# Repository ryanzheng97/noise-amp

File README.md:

# noise-amp

A very high gain (80db or x10000) differential AC signal amplifier (LNA, pre-amplifier, noise amplifier, etc.) board based on EEVBlog community design.

[Original post](https://www.eevblog.com/forum/beginners/question-about-preamp-for-measuring-noise/msg98285/#msg98285)

Board is a 100x100mm 4-layer PCB which falls into the cheap sample tier at JLCPCB or PCBWay.

# Specs
- Gain: 80db nominal
- Bandwidth: <= 1MHz
- Power: +-18 to 35VDC, unregulated
- Connector: SMA for signal input and output, 2.54mm THT pads for power input.

Test was done with a 1M to 100R resistor divider in front of the input. Signal was a sigle-ended sine wave, so one of the input is shorted to ground. Channel 3 shows original signal before resistor divider. Channel 1 shows amplified output.

# Notes
- Use high quality electrolytic capacitors
- Keep away from transformers
- You can replace op-amps with other models that you have or like
- Avoid ground loop when using
- Ground one input if using sigle-ended

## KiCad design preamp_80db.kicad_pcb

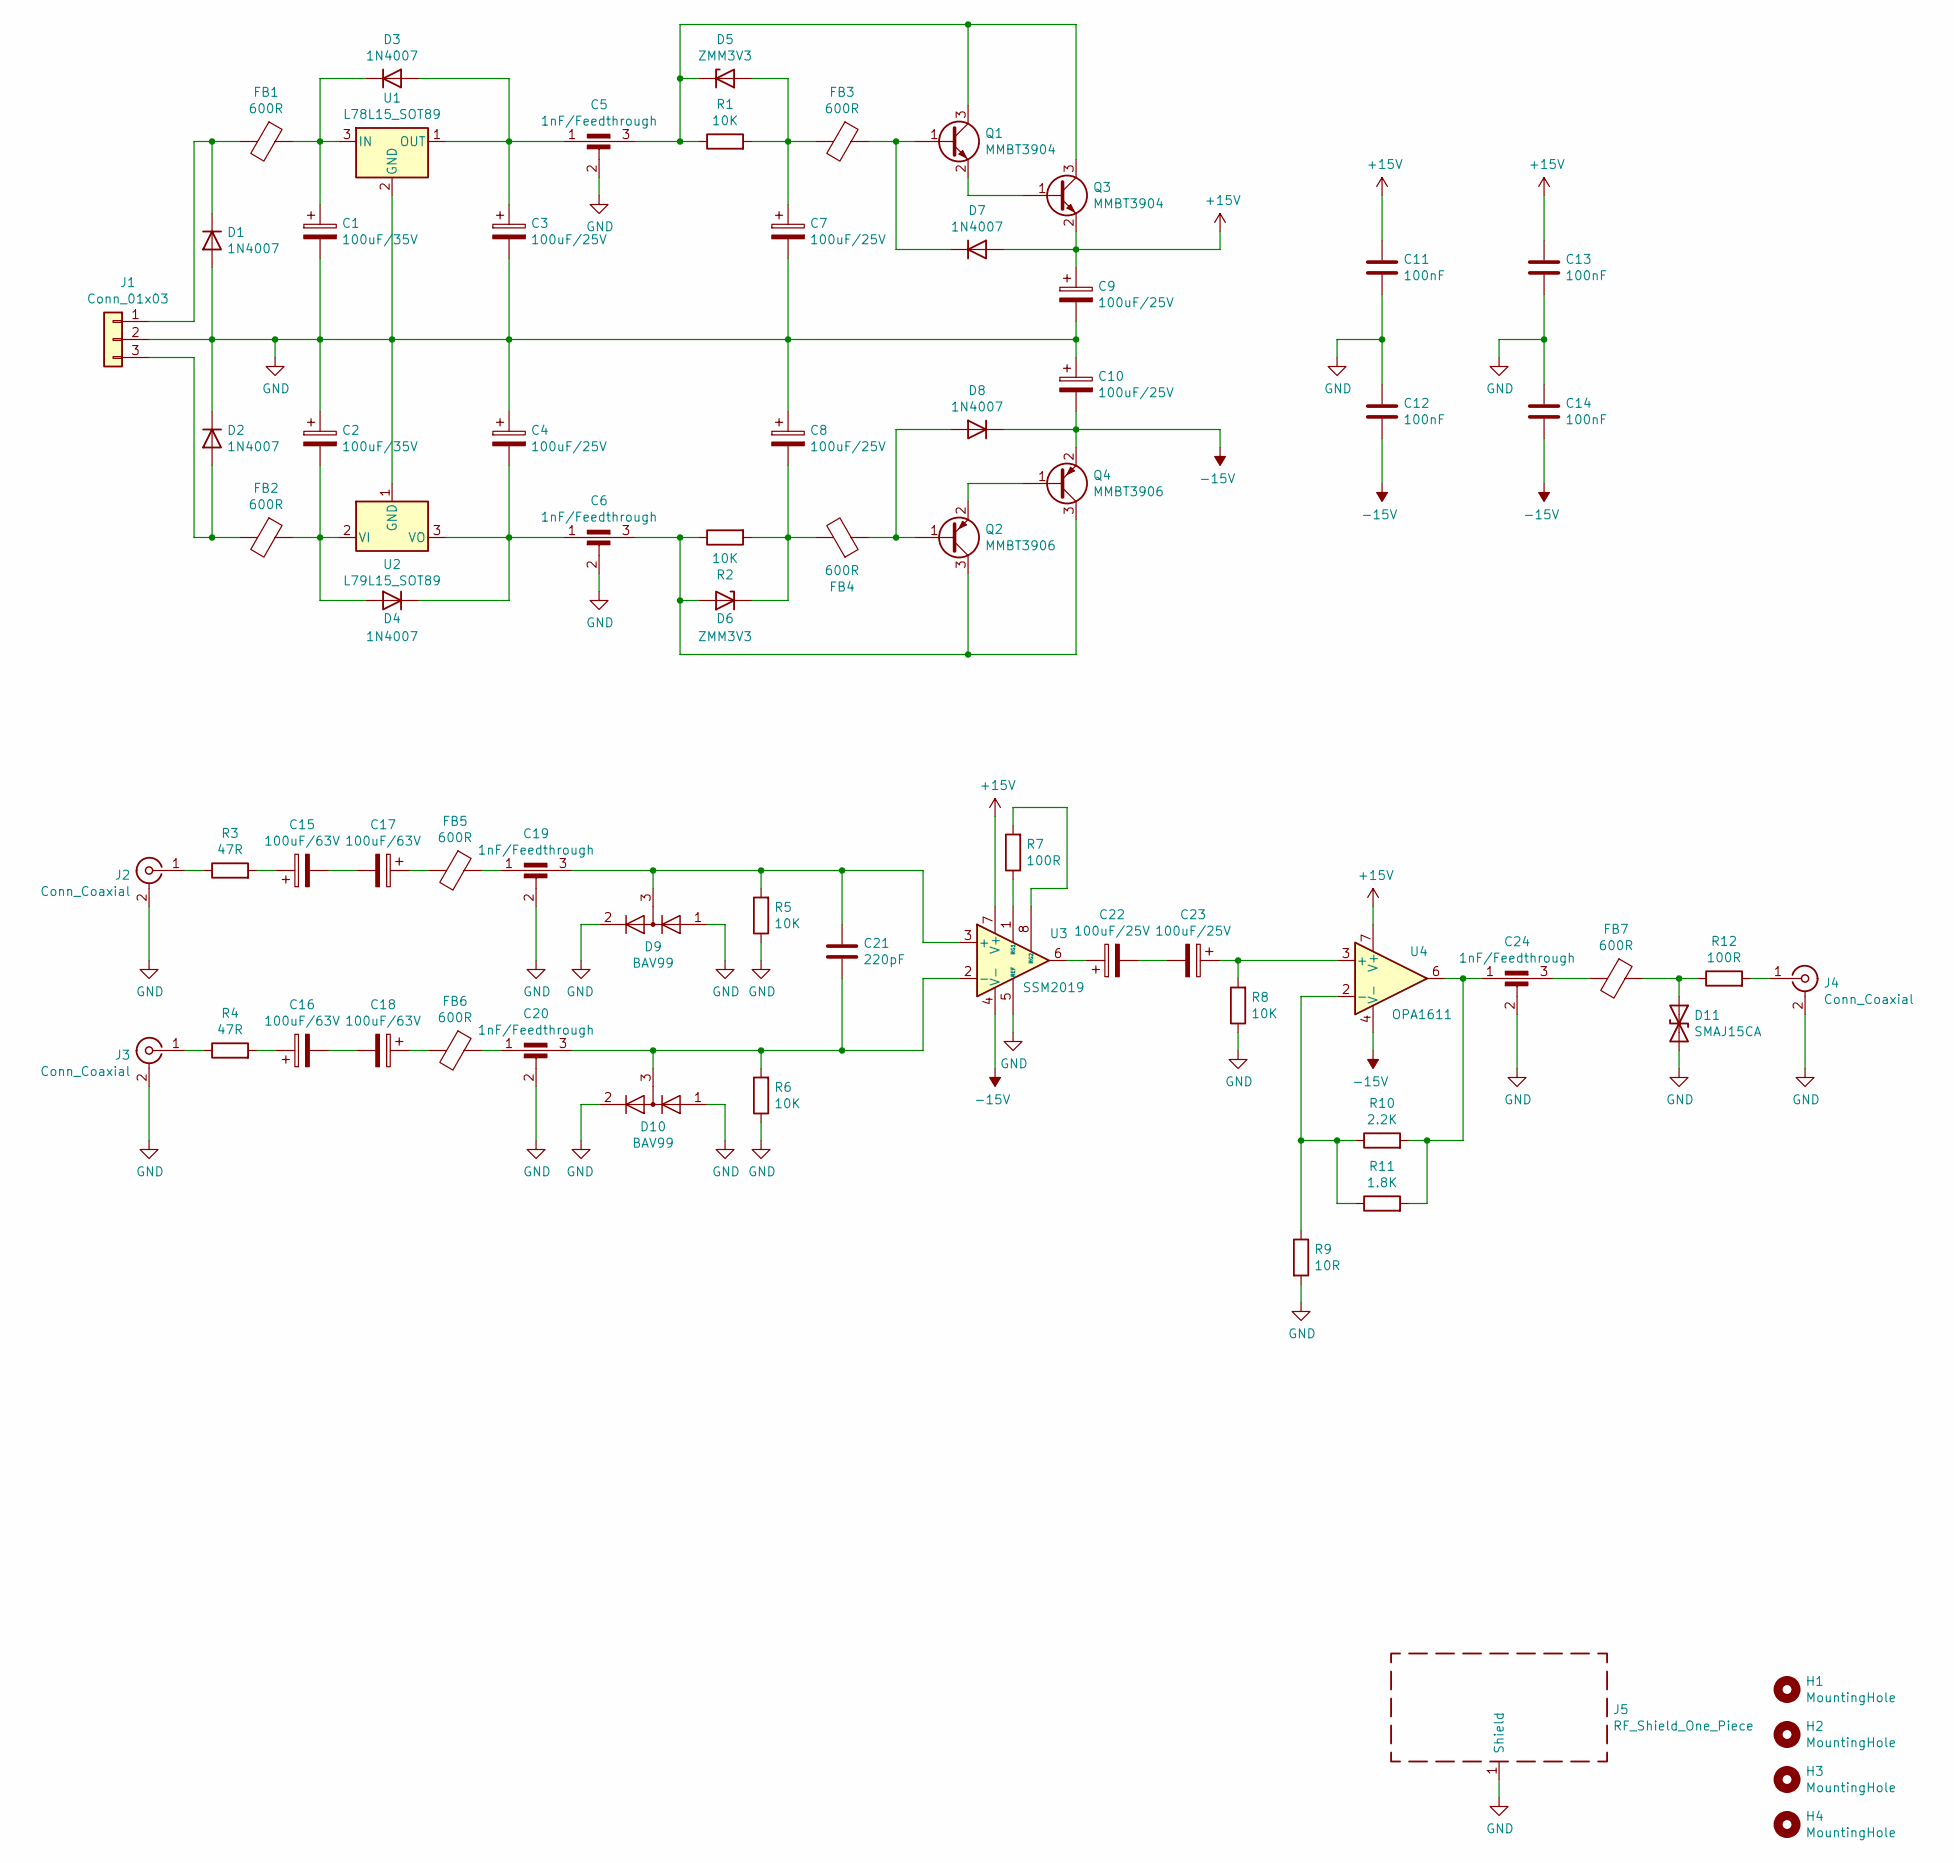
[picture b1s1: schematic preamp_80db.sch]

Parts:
C1, C2: 100uF/35V; CP_Radial_D6.3mm_P2.50mm
C3, C4, C7, C8, C9, C10, C22, C23: 100uF/25V; CP_Radial_D6.3mm_P2.50mm
C5, C6, C19, C20, C24: 1nF/Feedthrough; C_SMT_feedthrough_murata_0805
C11, C12, C13, C14: 100nF; C_0603_1608Metric
C15, C16, C17, C18: 100uF/63V; CP_Radial_D10.0mm_P2.50mm_P5.00mm
C21: 220pF; C_0603_1608Metric
D1, D2, D3, D4, D7, D8: 1N4007; D_SMA
D5, D6: ZMM3V3; D_MiniMELF
D9, D10: BAV99; SOT-23
D11: SMAJ15CA; D_SMA
FB1, FB2, FB3, FB4, FB5, FB6, FB7: 600R; L_0603_1608Metric
H1, H2, H3, H4: MountingHole; MountingHole_3.2mm_M3
J1: Conn_01x03; PinHeader_1x03_P2.54mm_Vertical
J2, J3, J4: Conn_Coaxial; SMA_Amphenol_132134_Vertical
J5: RF_Shield_One_Piece; Shielding_Can_THT_57x27x13mm
Q1, Q3: MMBT3904; SOT-23
Q2, Q4: MMBT3906; SOT-23
R1, R2, R5, R6, R8: 10K; R_0603_1608Metric
R3, R4: 47R; R_0603_1608Metric
R7, R12: 100R; R_0603_1608Metric
R9: 10R; R_0603_1608Metric
R10: 2.2K; R_0603_1608Metric
R11: 1.8K; R_0603_1608Metric
U1: L78L15_SOT89; SOT-89-3
U2: L79L15_SOT89; SOT-89-3
U3: SSM2019; SOIC-8_3.9x4.9mm_P1.27mm
U4: OPA1611; SOIC-8_3.9x4.9mm_P1.27mm

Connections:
+15V: C9.1, C11.1, C13.1, D7.2 (A), Q3.2 (E), U3.7 (V+), U4.7 (V+)
-15V: C10.2, C12.2, C14.2, D8.1 (K), Q4.2 (E), U3.4 (V-), U4.4 (V-)
GND: C1.2, C2.1, C3.2, C4.1, C5.2, C6.2, C7.2, C8.1, C9.2, C10.1, C11.2, C12.1, C13.2, C14.1, C19.2, C20.2, C24.2, D1.2 (A), D2.1 (K), D9.1 (K), D9.2 (A), D10.1 (K), D10.2 (A), D11.2 (A2), J1.2, J2.2 (Ext), J3.2 (Ext), J4.2 (Ext), J5.1, R5.1, R6.1, R8.1, R9.2, U1.2 (GND), U2.1 (GND), U3.5 (REF)
unnamed: C1.1, D3.1 (K), FB1.1, U1.3 (IN)
unnamed: C2.2, D4.2 (A), FB2.1, U2.2 (VI)
unnamed: C3.1, C5.1, D3.2 (A), U1.1 (OUT)
unnamed: C4.2, C6.1, D4.1 (K), U2.3 (VO)
unnamed: C5.3, D5.1 (K), Q1.3 (C), Q3.3 (C), R1.1
unnamed: C6.3, D6.2 (A), Q2.3 (C), Q4.3 (C), R2.1
unnamed: C7.1, D5.2 (A), FB3.2, R1.2
unnamed: C8.2, D6.1 (K), FB4.2, R2.2
unnamed: C15.1, R3.2
unnamed: C15.2, C17.2
unnamed: C16.1, R4.2
unnamed: C16.2, C18.2
unnamed: C17.1, FB5.2
unnamed: C18.1, FB6.2
unnamed: C19.1, FB5.1
unnamed: C19.3, C21.1, D9.3 (K), R5.2, U3.3 (+)
unnamed: C20.1, FB6.1
unnamed: C20.3, C21.2, D10.3 (K), R6.2, U3.2 (-)
unnamed: C22.1, U3.6
unnamed: C22.2, C23.2
unnamed: C23.1, R8.2, U4.3 (+)
unnamed: C24.1, R10.2, R11.2, U4.6
unnamed: C24.3, FB7.2
unnamed: D1.1 (K), FB1.2, J1.1
unnamed: D2.2 (A), FB2.2, J1.3
unnamed: D7.1 (K), FB3.1, Q1.1 (B)
unnamed: D8.2 (A), FB4.1, Q2.1 (B)
unnamed: D11.1 (A1), FB7.1, R12.1
unnamed: J2.1 (In), R3.1
unnamed: J3.1 (In), R4.1
unnamed: J4.1 (In), R12.2
unnamed: Q1.2 (E), Q3.1 (B)
unnamed: Q2.2 (E), Q4.1 (B)
unnamed: R7.1, U3.1 (RG1)
unnamed: R7.2, U3.8 (RG2)
unnamed: R9.1, R10.1, R11.1, U4.2 (-)

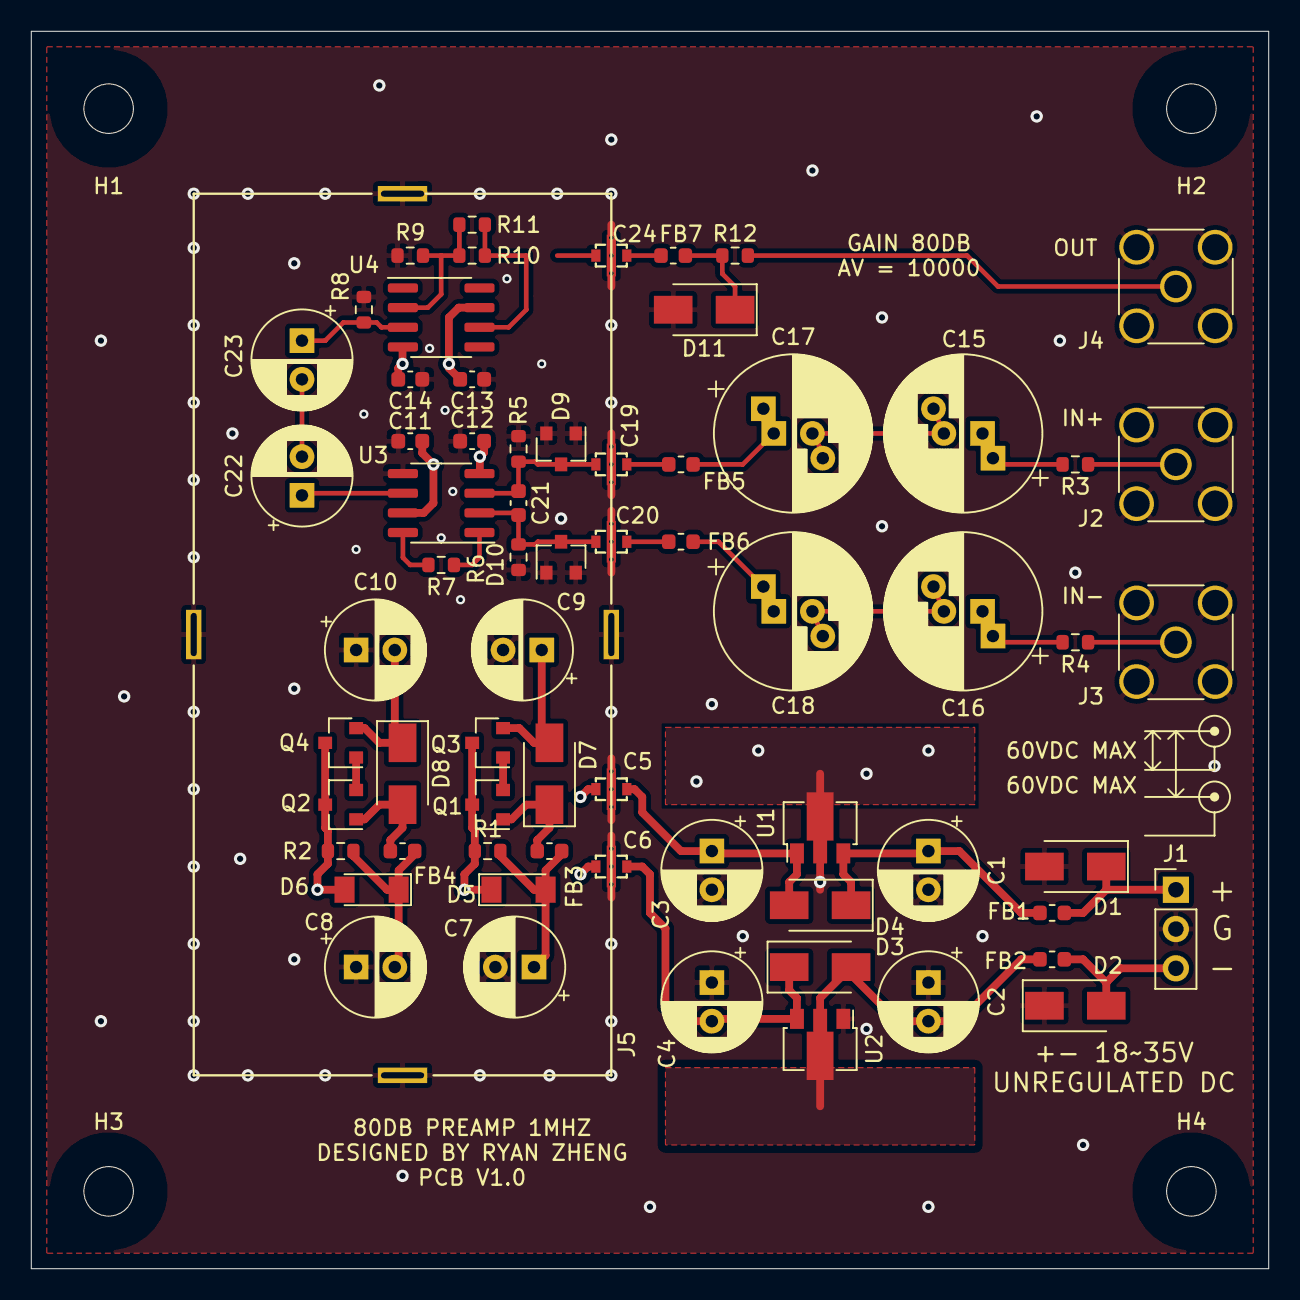
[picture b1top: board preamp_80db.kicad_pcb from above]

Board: 4 copper layers, 80.0 x 80.0 mm, 71 parts (0 on the bottom side), 39 nets.
